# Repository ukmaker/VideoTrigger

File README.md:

# VideoTrigger
My oscilloscope wouldn't trigger relibly on the video signal from my TMS9128 VDP, so I made this to help me work on my VDPtoTFT project. 

# Why?
Builders (and possessors) of retro-computers have many options for generating video. One of the chips used in computers in the early 80's was the TMS9918 family of Video Display Processors.

Because I had a semi-rational excuse for wanting to make my chip drive a small TFT display (the rabbit-hole starts [here](https://github.com/ukmaker/VDPtoTFT)), I needed to be able to view the video outputs on my oscilloscope. My 'scope has a "Video Trigger" mode, which I gleefully enabled in anticipation of a nice, rock-solid display. No dice. No triggering of any sort was happening. This turns out not to be (totally) the fault of my 'scope - a Hantek DSO1502P. I think this is because the output from the chip isn't really a conformant video signal. I'm not entirely sure why, unless the scope expects "normal" voltage levels which take quite some work to produce from what the chip outputs.

So, in order to view the signals properly, I needed an external trigger signal. Hence this project. It uses the well known LM1881 sync separator IC to derive horizontal and vertical sync from the chip's "Y" output. These in turn feed an Atemga328P - programmed using the Arduino framework - which allows user selection of 
  - which edge of hsync to trigger off
  - which line to trigger off
These are selectable by pushing and turning a rotary encoder, and the setting is display on a small OLED display.

The output from the LM1881 is used to clock a pair of JK flip-flops - one for the positive and one for the negative edge of the sync signal - and the negative-edge clock is inverted using a transistor. The appropriate flip-flop is enabled by the Atmega328 for the duration of the chosen line. The outputs are ORed together using diode logic and a resistor.

Here is the circuit built on a bit of protoboard. It is powered from the scope's USB port. Input signal is on the left, trigger output is on the right.
[The Video Trigger](./images/VideoTrigger.JPG)

This picture shows the video signal and the trigger signal. Note that the trigger output from my circuit is the falling edge of the blue signal - the rising edge occurs an arbitrary time after the horizontal trigger signal, and is a very slow edge.
[Triggering on the falling edge](./images/NegativeTrigger.png)

And in this image you can see the slow rising edge of the trigger signal
[Triggering on the rising edge](./images/PositiveTrigger.png)

# Is It Any Good?
Well, it's good enough for me :-)

The input buffer is tailored to the output of the VDP. If the signal you use as the input does not have a DC offset of 2V, you'll need to bias the transistor up and add an input decoupling capacitor.

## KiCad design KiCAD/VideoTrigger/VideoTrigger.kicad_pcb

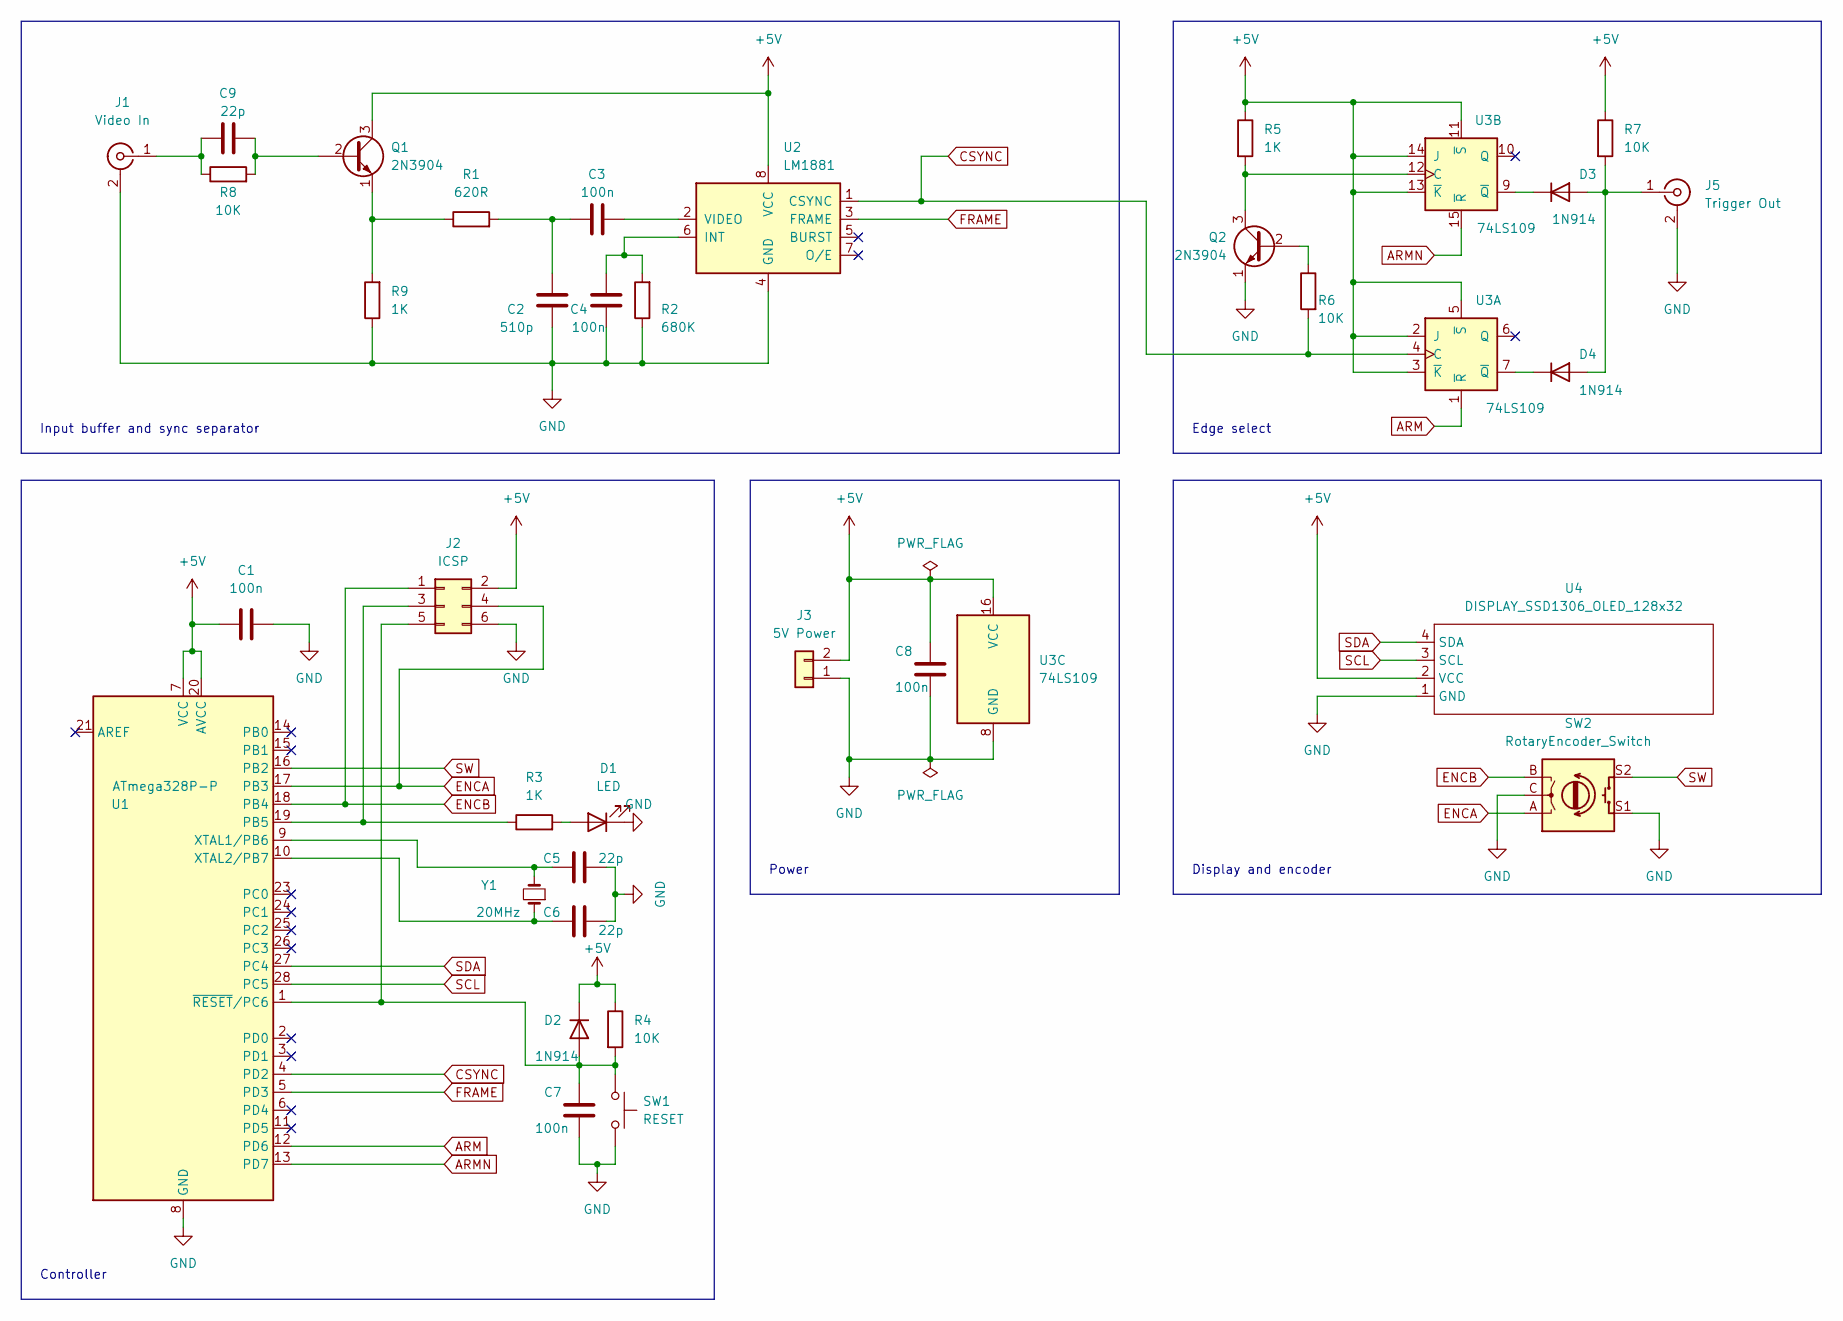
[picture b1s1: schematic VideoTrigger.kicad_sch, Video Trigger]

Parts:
C1, C3, C4, C7, C8: 100n; C_Disc_D4.3mm_W1.9mm_P5.00mm
C2: 510p; C_Disc_D4.3mm_W1.9mm_P5.00mm
C5, C6, C9: 22p; C_Disc_D4.3mm_W1.9mm_P5.00mm
D1: LED; LED_D3.0mm
D2, D3, D4: 1N914; D_DO-34_SOD68_P7.62mm_Horizontal
J1: Video In; SMA_Amphenol_901-144_Vertical
J2: ICSP; PinHeader_2x03_P2.54mm_Vertical
J3: 5V Power; TerminalBlock_bornier-2_P5.08mm
J5: Trigger Out; SMA_Amphenol_901-144_Vertical
Q1, Q2: 2N3904; TO-92L_Inline_Wide
R1: 620R; R_Axial_DIN0207_L6.3mm_D2.5mm_P7.62mm_Horizontal
R2: 680K; R_Axial_DIN0207_L6.3mm_D2.5mm_P7.62mm_Horizontal
R3, R5, R9: 1K; R_Axial_DIN0207_L6.3mm_D2.5mm_P7.62mm_Horizontal
R4, R6, R7, R8: 10K; R_Axial_DIN0207_L6.3mm_D2.5mm_P7.62mm_Horizontal
SW1: RESET; SW_TH_Tactile_Omron_B3F-10xx
SW2: RotaryEncoder_Switch; RotaryEncoder_Alps_EC11E-Switch_Vertical_H20mm
U1: ATmega328P-P; DIP-28_W7.62mm
U2: LM1881; DIP-8_W7.62mm_LongPads
U3: 74LS109; DIP-16_W7.62mm_LongPads
U4: DISPLAY_SSD1306_OLED_128x32; PinHeader_1x04_P2.54mm_Vertical
Y1: 20MHz; Crystal_HC49-U_Vertical

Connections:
+5V: C1.1, C8.1, D2.1 (K), J2.2, J3.2, Q1.3 (C), R4.1, R5.1, R7.1, U1.7 (VCC), U1.20 (AVCC), U2.8 (VCC), U3.2 (J), U3.3 (~K), U3.5 (~S), U3.11 (~S), U3.13 (~K), U3.14 (J), U3.16 (VCC), U4.2 (VCC)
ARM: U1.12 (PD6), U3.1 (~R)
ARMN: U1.13 (PD7), U3.15 (~R)
CSYNC: R6.2, U1.4 (PD2), U2.1 (CSYNC), U3.4 (C)
ENCA: J2.4, SW2.A, U1.17 (PB3)
ENCB: J2.1, SW2.B, U1.18 (PB4)
FRAME: U1.5 (PD3), U2.3 (FRAME)
GND: C1.2, C2.2, C4.2, C5.1, C6.1, C7.2, C8.2, D1.1 (K), J1.2 (Ext), J2.6, J3.1, J5.2 (Ext), Q2.1 (E), R2.1, R9.1, SW1.2, SW2.C, SW2.S1, U1.8 (GND), U1.22 (GND), U2.4 (GND), U3.8 (GND), U4.1 (GND)
unnamed: C2.1, C3.2, R1.2
unnamed: C3.1, U2.2 (VIDEO)
unnamed: C4.1, R2.2, U2.6 (INT)
unnamed: C5.2, U1.9 (XTAL1/PB6), Y1.2
unnamed: C6.2, U1.10 (XTAL2/PB7), Y1.1
unnamed: C7.1, D2.2 (A), J2.5, R4.2, SW1.1, U1.1 (~RESET/PC6)
unnamed: C9.1, Q1.2 (B), R8.2
unnamed: C9.2, J1.1 (In), R8.1
unnamed: D3.1 (K), U3.9 (~Q)
unnamed: D3.2 (A), D4.2 (A), J5.1 (In), R7.2
unnamed: D4.1 (K), U3.7 (~Q)
unnamed: J2.3, R3.1, U1.19 (PB5)
unnamed: Q1.1 (E), R1.1, R9.2
unnamed: D1.2 (A), R3.2
unnamed: Q2.3 (C), R5.2, U3.12 (C)
unnamed: Q2.2 (B), R6.1
SCL: U1.28 (PC5), U4.3 (SCL)
SDA: U1.27 (PC4), U4.4 (SDA)
SW: SW2.S2, U1.16 (PB2)

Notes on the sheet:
Controller
Display and encoder
Power
Edge select
Input buffer and sync separator

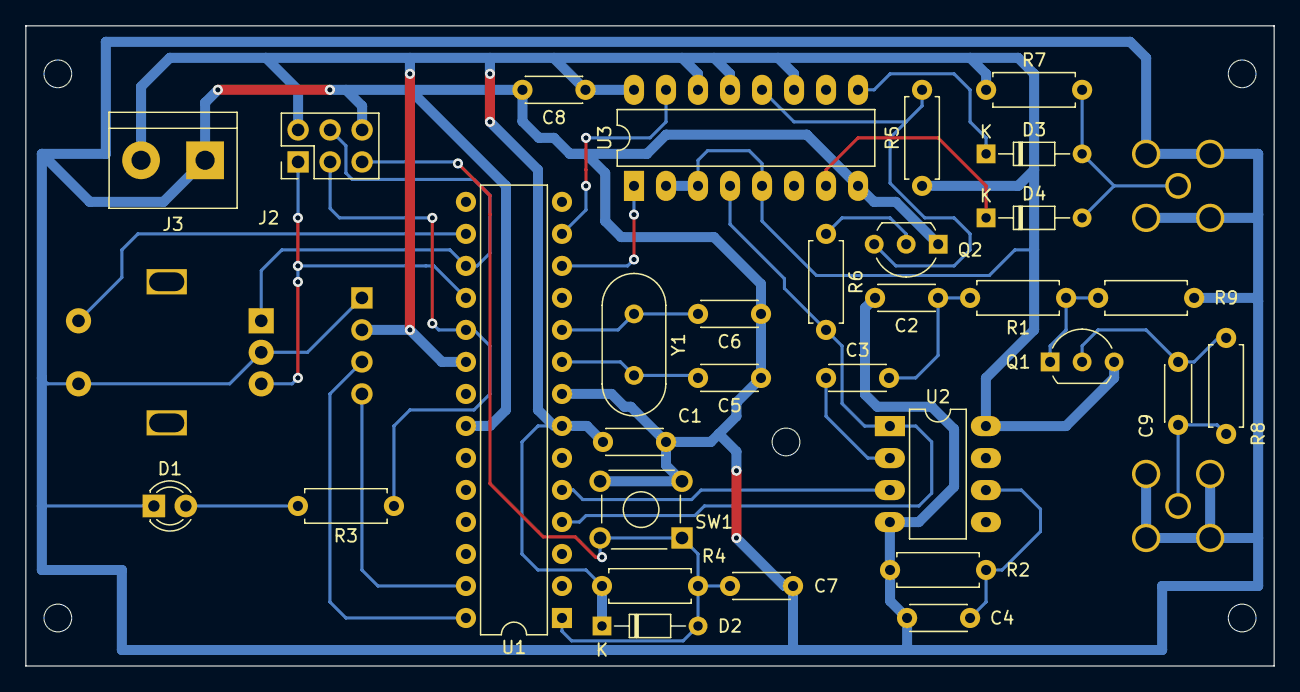
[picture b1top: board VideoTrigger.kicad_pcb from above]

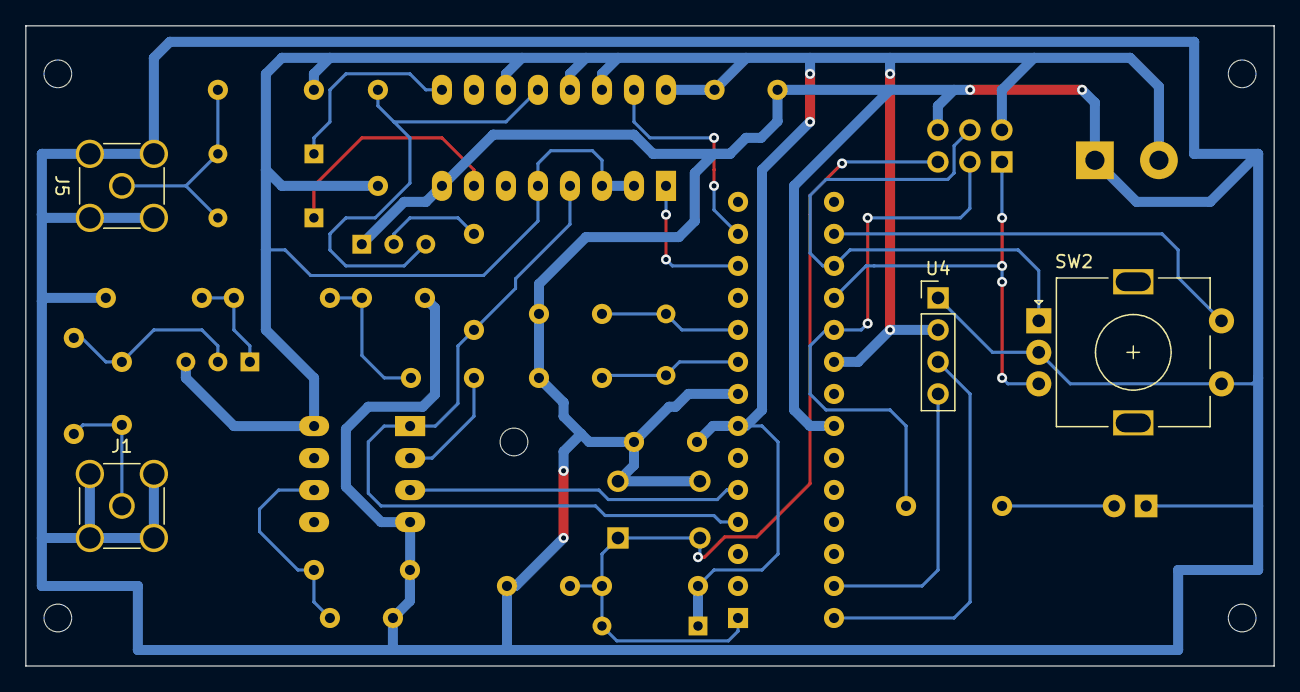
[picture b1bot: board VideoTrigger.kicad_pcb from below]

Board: 2 copper layers, 99.1 x 50.8 mm, 35 parts (4 on the bottom side), 27 nets.

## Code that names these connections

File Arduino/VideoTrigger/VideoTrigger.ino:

#include <EncoderButton.h>
#include <SPI.h>
#include <Wire.h>
#include <Adafruit_GFX.h>
#include <Adafruit_SSD1306.h>


#define INTER_FRAME_LINES 11

// Actually 312.5
#define PAL_LINES 313
#define PAL_VISIBLE_LINES 288

// Actually 262.5
#define NTSC_LINES 263
#define NTSC_VISIBLE_LINES 238
#define ARM 7
#define ARMN 6
#define ENCA 11
#define ENCB 12
#define ENCC 10
#define ARMND (1<<7)
#define ARMD (1<<6)

#define SCREEN_WIDTH 128 // OLED display width, in pixels
#define SCREEN_HEIGHT 32 // OLED display height, in pixels
#define OLED_RESET     -1 // Reset pin # (or -1 if sharing Arduino reset pin)
#define SCREEN_ADDRESS 0x3C ///< See datasheet for Address; 0x3D for 128x64, 0x3C for 128x32
Adafruit_SSD1306 display(SCREEN_WIDTH, SCREEN_HEIGHT, &Wire, OLED_RESET);


volatile int line = 0;
volatile int lines = 0;
volatile int trigger = 24;
volatile int maxlines = 0;
volatile bool falling = false;
volatile bool armed = false;
volatile uint8_t arm = ARMD;
volatile uint8_t frames = 0;
int lastTrigger = 0;
int lastPolarity = false;


EncoderButton eb1(ENCA, ENCB, ENCC);

void onEb1Clicked(EncoderButton& eb) {
  falling = !falling;
  detachInterrupt(digitalPinToInterrupt(2));
  if (falling) {
    attachInterrupt(digitalPinToInterrupt(2), hsync, FALLING);
    arm = ARMD;
  } else {
    attachInterrupt(digitalPinToInterrupt(2), hsync, RISING);
    arm = ARMND;
  }
  maxlines = 0;
}

void onEb1Encoder(EncoderButton& eb) {
  long pos = eb.position();
  if (pos > maxlines) pos = 1;
  if (pos <= 0) pos = maxlines;
  trigger = pos;
}

void onButton1LongPress(EncoderButton& eb) {
  trigger = 1;
}

void setup() {

  pinMode(ARM, OUTPUT);
  pinMode(ARMN, OUTPUT);
  digitalWrite(ARM, HIGH);
  digitalWrite(ARMN, LOW);
  // setup the encoder and screen

  //Link the event(s) to your function
  eb1.setClickHandler(onEb1Clicked);
  eb1.setEncoderHandler(onEb1Encoder);
  eb1.setLongPressHandler(onButton1LongPress, false);

  display.begin(SSD1306_SWITCHCAPVCC, SCREEN_ADDRESS);
  display.display();
  display.clearDisplay();

  display.setTextSize(2); // Draw 2X-scale text
  display.setTextColor(SSD1306_WHITE);
  display.setCursor(0, 0);
  display.println(("Video"));
  display.println(("Trigger"));
  display.display();
  delay(1000);
  display.setCursor(10, 0);
  eb1.resetPosition(trigger);
  attachInterrupt(digitalPinToInterrupt(3), vsync, FALLING);
  attachInterrupt(digitalPinToInterrupt(2), hsync, FALLING);
}

void loop() {
  // put your main code here, to run repeatedly:
  // reset the line count every now and then in case we got a glitch
  if(frames == 0) {
    maxlines = 0;
  }
  eb1.update();
  if (lastTrigger != trigger || lastPolarity != falling) {
    lastTrigger = trigger;
    lastPolarity = falling;

    eb1.resetPosition(trigger);

    display.clearDisplay();
    display.setCursor(0, 0);

    if (!falling) {
      display.print("\\_");
    } else {
      display.print("_/");
    }
    display.print(trigger, DEC);
    display.print("/");
    display.print(maxlines);
    display.display();
  }
}


void hsync() {

  if (line == trigger) {
    PORTD |= arm;
  } else {
    PORTD &= 0x3f;
  }

  lines++;
  line++;
  if (line > maxlines) line = 1;
}

void vsync() {
  line = maxlines - INTER_FRAME_LINES;
  if (lines > maxlines) maxlines = lines;
  lines = 0;
  frames++;
}

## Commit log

2022-09-11 Initial import
2022-10-02 Updated README and schematic
2022-10-04 Added input buffering, updated README
2022-10-04 Added PCB layout. Some signal changes to make routing easier
